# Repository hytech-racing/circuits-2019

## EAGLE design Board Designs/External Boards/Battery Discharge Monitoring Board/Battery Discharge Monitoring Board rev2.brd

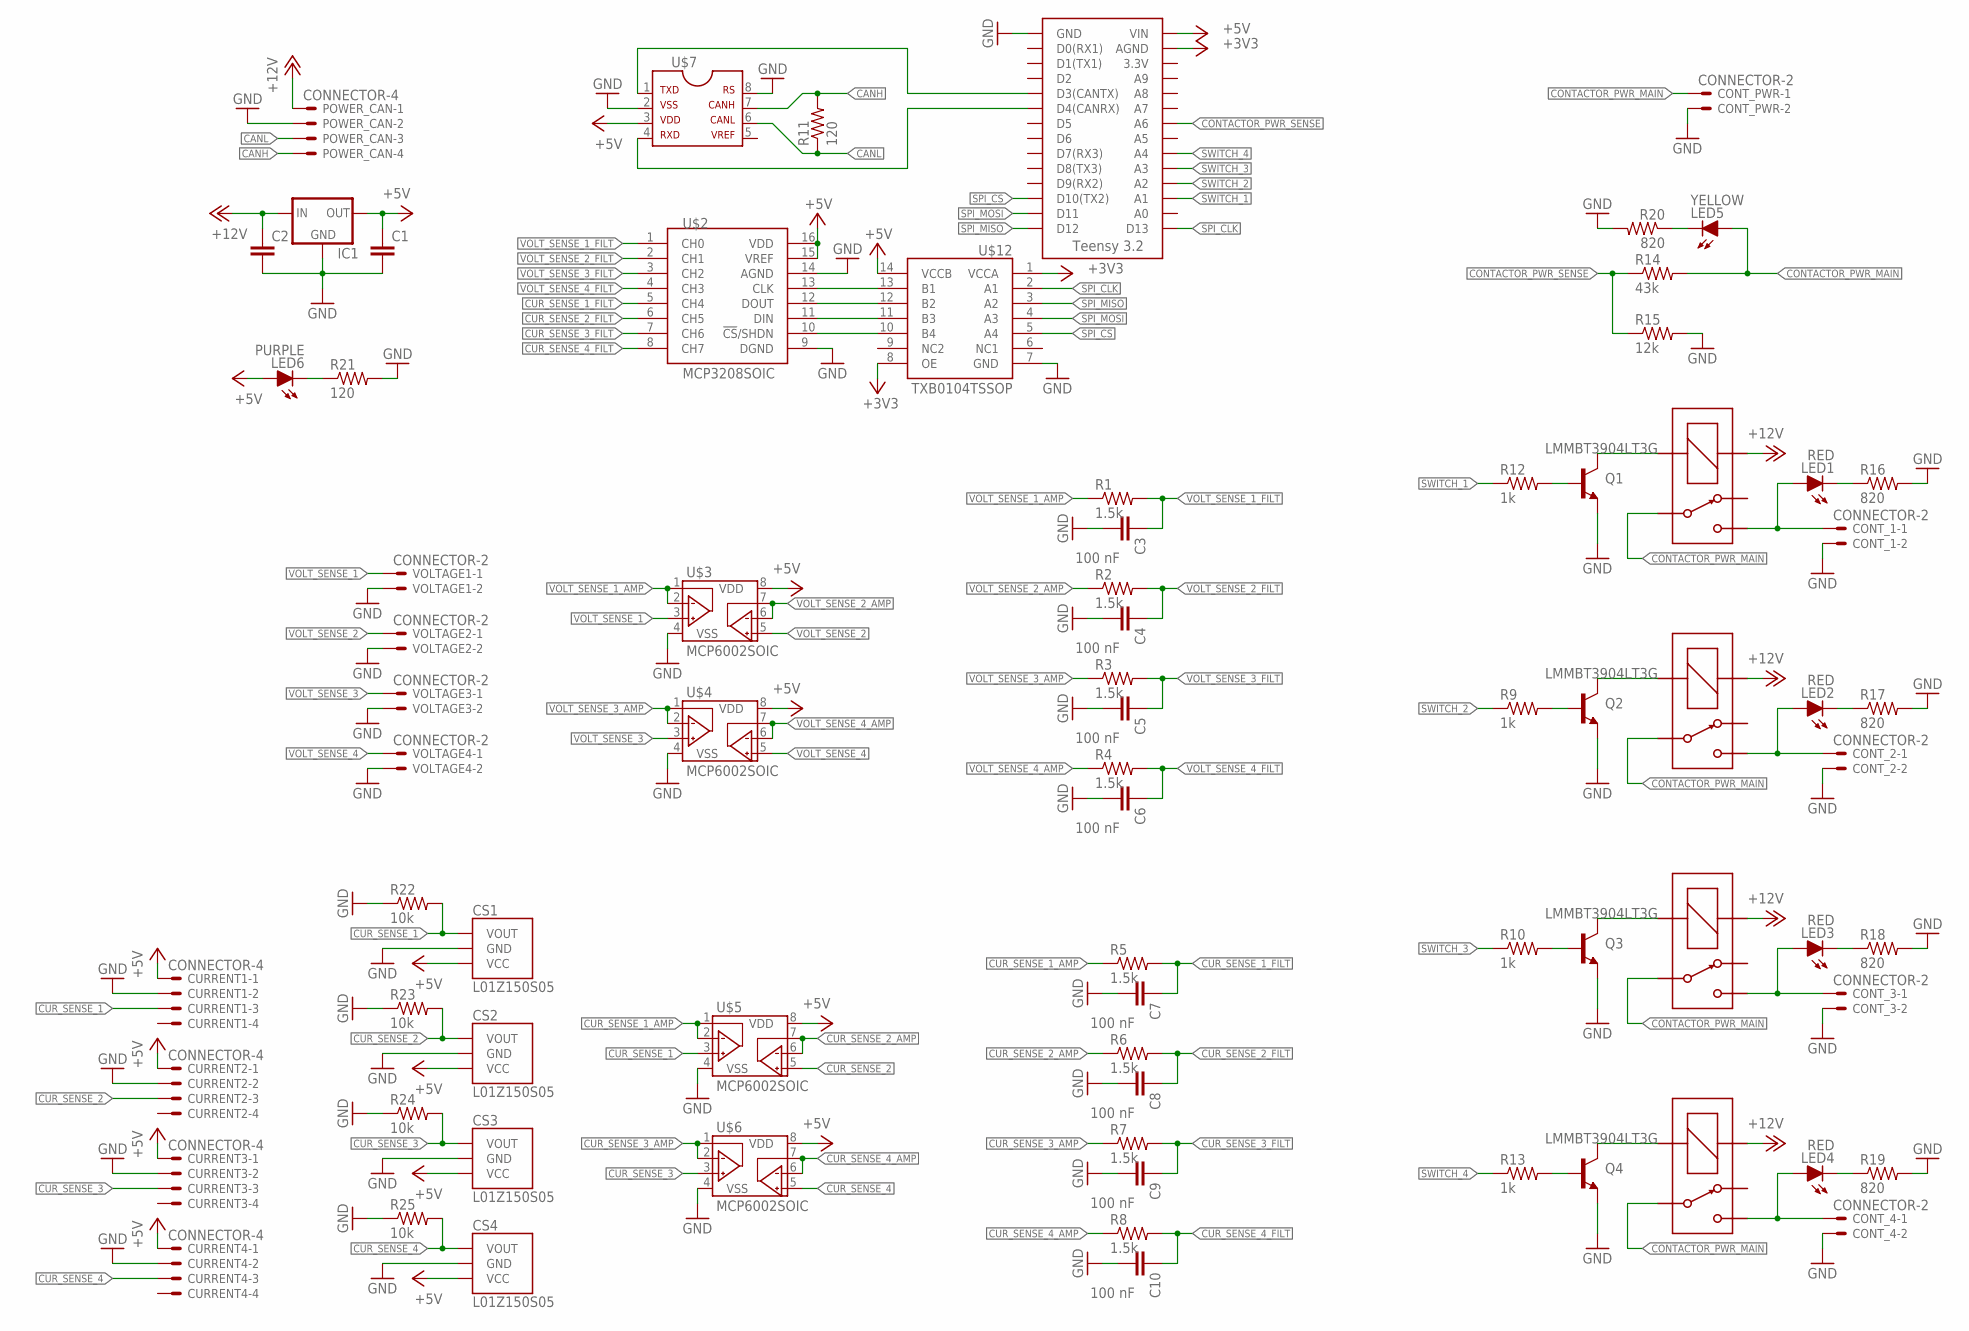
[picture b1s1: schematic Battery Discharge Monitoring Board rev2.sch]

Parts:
C1, C2: CAP0805; 0805
C3, C4, C5, C6, C7, C8, C9, C10: 100 nF; 0805
CONT_1, CONT_2, CONT_3, CONT_4: CONNECTOR-2; MINIFIT_5566-2
CONT_PWR: CONNECTOR-2; MINIFIT_5566-2
CS1, CS2, CS3, CS4: L01Z150S05
CURRENT1, CURRENT2, CURRENT3, CURRENT4: CONNECTOR-4; MINIFIT_5566-4
IC1: 5VREG_L7805SPACED; TO-220-SPACED
LED1, LED2, LED3, LED4: RED; LED-805
LED5: YELLOW; LED-805
LED6: PURPLE; LED-805
POWER_CAN: CONNECTOR-4; MINIFIT_5566-4
Q1, Q2, Q3, Q4: LMMBT3904LT3G; SOT23
R1, R2, R3, R4, R5, R6, R7, R8: 1.5k; 0805
R9, R10, R12, R13: 1k; 0805
R11, R21: 120; 0805
R14: 43k; 0805
R15: 12k; 0805
R16, R17, R18, R19, R20: 820; 0805
R22, R23, R24, R25: 10k; 0805
U$1: TEENSY_3.2_SIMPLE
U$2: MCP3208SOIC; SOIC-16
U$3, U$4, U$5, U$6: MCP6002SOIC; SOIC-08
U$7: MCP2551; SOIC-08
U$8, U$9, U$10, U$11: G5LE; ZF112
U$12: TXB0104TSSOP; TSSOP-14
VOLTAGE1, VOLTAGE2, VOLTAGE3, VOLTAGE4: CONNECTOR-2; MINIFIT_5566-2

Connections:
+3V3: U$1.AGND, U$12.1 (VCCA), U$12.8 (OE)
+5V: C1.1, CS1.3 (VCC), CS2.3 (VCC), CS3.3 (VCC), CS4.3 (VCC), CURRENT1.1, CURRENT2.1, CURRENT3.1, CURRENT4.1, IC1.3 (OUT), LED6.A, U$1.VIN, U$2.15 (VREF), U$2.16 (VDD), U$3.8 (VDD), U$4.8 (VDD), U$5.8 (VDD), U$6.8 (VDD), U$7.3, U$12.14 (VCCB)
+12V: C2.1, IC1.1 (IN), POWER_CAN.1, U$8.1 (COIL+), U$9.1 (COIL+), U$10.1 (COIL+), U$11.1 (COIL+)
CANH: POWER_CAN.4, R11.2, U$7.7
CANL: POWER_CAN.3, R11.1, U$7.6
CONTACTOR_PWR_1: CONT_1.1, LED1.A, U$8.S
CONTACTOR_PWR_2: CONT_2.1, LED2.A, U$9.S
CONTACTOR_PWR_3: CONT_3.1, LED3.A, U$10.S
CONTACTOR_PWR_4: CONT_4.1, LED4.A, U$11.S
CONTACTOR_PWR_MAIN: CONT_PWR.1, LED5.A, R14.2, U$8.P, U$9.P, U$10.P, U$11.P
CONTACTOR_PWR_SENSE: R14.1, R15.1, U$1.A6
CUR_SENSE_1: CS1.1 (VOUT), CURRENT1.3, R22.2, U$5.3 (VINA+)
CUR_SENSE_1_AMP: R5.1, U$5.1 (VOUTA), U$5.2 (VINA-)
CUR_SENSE_1_FILT: C7.1, R5.2, U$2.5 (CH4)
CUR_SENSE_2: CS2.1 (VOUT), CURRENT2.3, R23.2, U$5.5 (VINB+)
CUR_SENSE_2_AMP: R6.1, U$5.6 (VINB-), U$5.7 (VOUTB)
CUR_SENSE_2_FILT: C8.1, R6.2, U$2.6 (CH5)
CUR_SENSE_3: CS3.1 (VOUT), CURRENT3.3, R24.2, U$6.3 (VINA+)
CUR_SENSE_3_AMP: R7.1, U$6.1 (VOUTA), U$6.2 (VINA-)
CUR_SENSE_3_FILT: C9.1, R7.2, U$2.7 (CH6)
CUR_SENSE_4: CS4.1 (VOUT), CURRENT4.3, R25.2, U$6.5 (VINB+)
CUR_SENSE_4_AMP: R8.1, U$6.6 (VINB-), U$6.7 (VOUTB)
CUR_SENSE_4_FILT: C10.1, R8.2, U$2.8 (CH7)
GND: C1.2, C2.2, C3.2, C4.2, C5.2, C6.2, C7.2, C8.2, C9.2, C10.2, CONT_1.2, CONT_2.2, CONT_3.2, CONT_4.2, CONT_PWR.2, CS1.2 (GND), CS2.2 (GND), CS3.2 (GND), CS4.2 (GND), CURRENT1.2, CURRENT2.2, CURRENT3.2, CURRENT4.2, IC1.2 (GND), POWER_CAN.2, Q1.2 (EMITTER), Q2.2 (EMITTER), Q3.2 (EMITTER), Q4.2 (EMITTER), R15.2, R16.2, R17.2, R18.2, R19.2, R20.2, R21.2, R22.1, R23.1, R24.1, R25.1, U$1.GND, U$2.9 (DGND), U$2.14 (AGND), U$3.4 (VSS), U$4.4 (VSS), U$5.4 (VSS), U$6.4 (VSS), U$7.2, U$7.8, U$12.7 (GND), VOLTAGE1.2, VOLTAGE2.2, VOLTAGE3.2, VOLTAGE4.2
unnamed: U$1.D3(CANTX), U$7.1
unnamed: U$1.D4(CANRX), U$7.4
unnamed: Q2.1 (BASE), R9.2
unnamed: Q1.1 (BASE), R12.2
unnamed: Q1.3 (COLLECTOR), U$8.2 (COIL-)
unnamed: Q2.3 (COLLECTOR), U$9.2 (COIL-)
unnamed: Q3.1 (BASE), R10.2
unnamed: Q3.3 (COLLECTOR), U$10.2 (COIL-)
unnamed: Q4.1 (BASE), R13.2
unnamed: Q4.3 (COLLECTOR), U$11.2 (COIL-)
unnamed: LED2.C, R17.1
unnamed: LED1.C, R16.1
unnamed: LED3.C, R18.1
unnamed: LED4.C, R19.1
unnamed: LED5.C, R20.1
unnamed: LED6.C, R21.1
SPI_CLK: U$1.D13, U$2.13 (CLK), U$12.2 (A1), U$12.13 (B1)
SPI_CS: U$1.D10(TX2), U$2.10 (!CS!/SHDN), U$12.5 (A4), U$12.10 (B4)
SPI_MISO: U$1.D12, U$2.12 (DOUT), U$12.3 (A2), U$12.12 (B2)
SPI_MOSI: U$1.D11, U$2.11 (DIN), U$12.4 (A3), U$12.11 (B3)
SWITCH_1: R12.1, U$1.A1
SWITCH_2: R9.1, U$1.A2
SWITCH_3: R10.1, U$1.A3
SWITCH_4: R13.1, U$1.A4
VOLT_SENSE_1: U$3.3 (VINA+), VOLTAGE1.1
VOLT_SENSE_1_AMP: R1.1, U$3.1 (VOUTA), U$3.2 (VINA-)
VOLT_SENSE_1_FILT: C3.1, R1.2, U$2.1 (CH0)
VOLT_SENSE_2: U$3.5 (VINB+), VOLTAGE2.1
VOLT_SENSE_2_AMP: R2.1, U$3.6 (VINB-), U$3.7 (VOUTB)
VOLT_SENSE_2_FILT: C4.1, R2.2, U$2.2 (CH1)
VOLT_SENSE_3: U$4.3 (VINA+), VOLTAGE3.1
VOLT_SENSE_3_AMP: R3.1, U$4.1 (VOUTA), U$4.2 (VINA-)
VOLT_SENSE_3_FILT: C5.1, R3.2, U$2.3 (CH2)
VOLT_SENSE_4: U$4.5 (VINB+), VOLTAGE4.1
VOLT_SENSE_4_AMP: R4.1, U$4.6 (VINB-), U$4.7 (VOUTB)
VOLT_SENSE_4_FILT: C6.1, R4.2, U$2.4 (CH3)

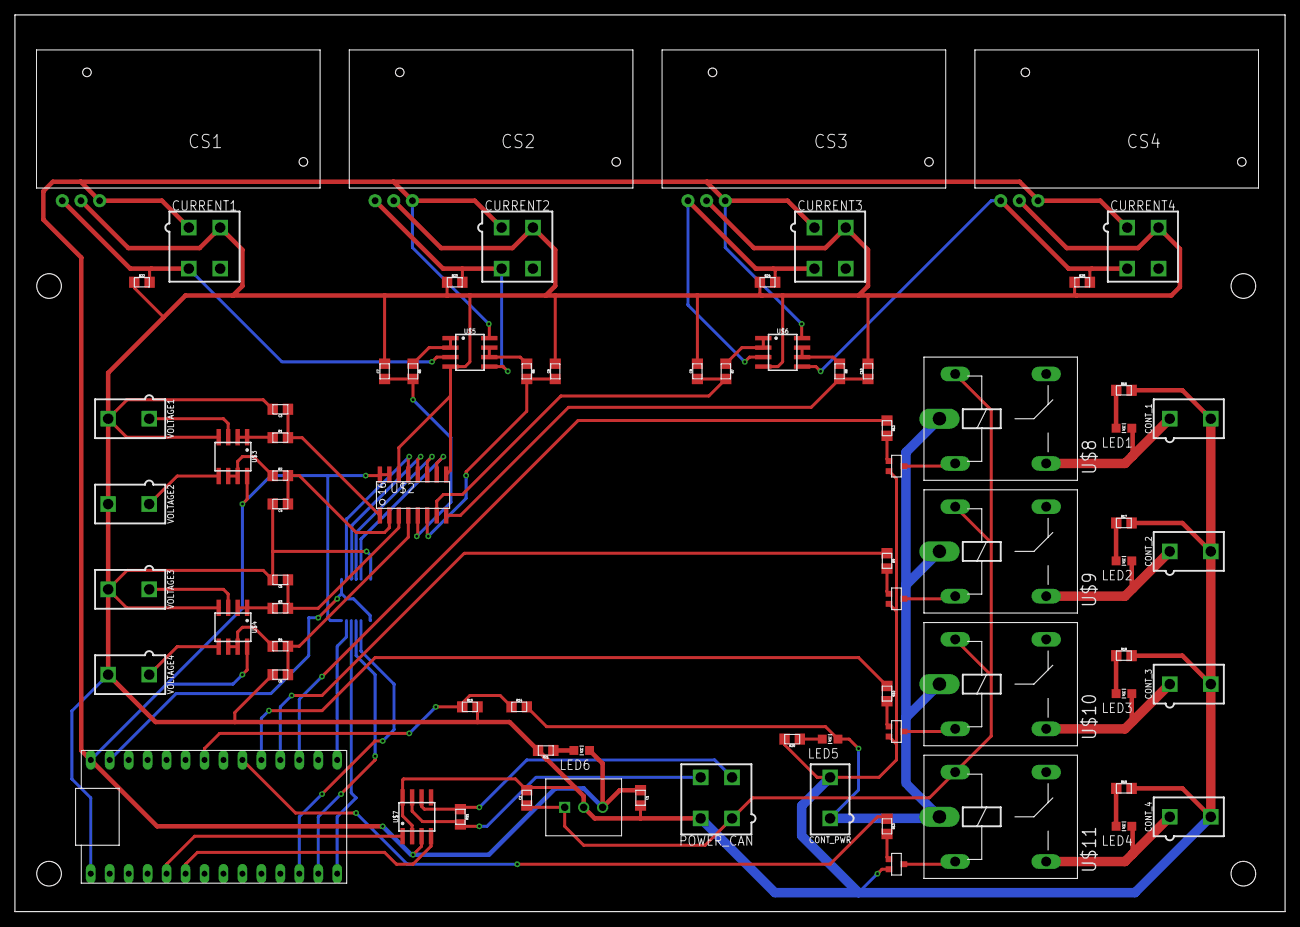
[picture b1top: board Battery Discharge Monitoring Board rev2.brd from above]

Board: 2 copper layers, 170.2 x 120.1 mm, 76 parts (1 on the bottom side), 60 nets.

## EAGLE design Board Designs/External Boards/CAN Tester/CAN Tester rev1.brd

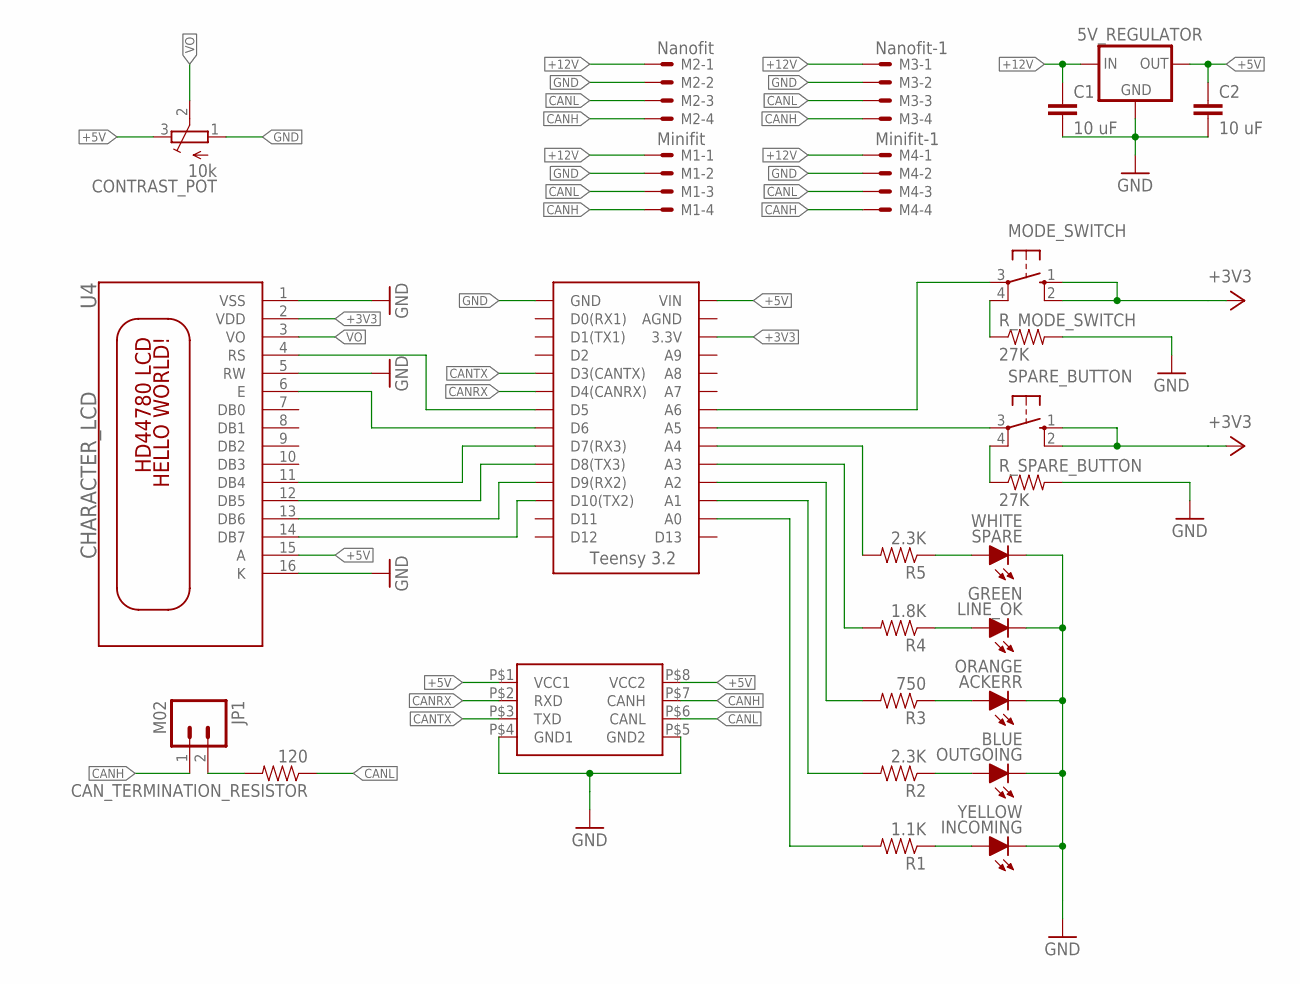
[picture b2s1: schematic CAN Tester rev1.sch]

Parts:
5V_REGULATOR: 5VREG_LM340-NLM340MPX-5.0/NOPB; SOT223
ACKERR: ORANGE; LED-805
C1, C2: 10 uF; 0805
CAN_TERMINATION_RESISTOR: 120; 0805
CONTRAST_POT: 10k; TRIM-3386
INCOMING: YELLOW; LED-805
JP1: M02; 1X02
LINE_OK: GREEN; LED-805
M1: Minifit; MINIFIT_5566-4
M2: Nanofit; NANO-FIT_VERTICAL-4
M3: Nanofit-1; NANO-FIT_VERTICAL-4
M4: Minifit-1; MINIFIT_5566-4
MODE_SWITCH: BTN_10-XX; B3F-10XX
OUTGOING: BLUE; LED-805
R1: 1.1K; 0805
R2, R5: 2.3K; 0805
R3: 750; 0805
R4: 1.8K; 0805
R_MODE_SWITCH: 27K; 0805
R_SPARE_BUTTON: 27K; 0805
SPARE: WHITE; LED-805
SPARE_BUTTON: BTN_10-XX; B3F-10XX
U1: ISOLATED CAN TRANSCIEVER; DUB8
U3: TEENSY_3.2_SIMPLE
U4: CHARACTER_LCD; LCD1602

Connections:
+3V3: MODE_SWITCH.1 (S), MODE_SWITCH.2 (S1), SPARE_BUTTON.1 (S), SPARE_BUTTON.2 (S1), U3.3.3V, U4.2 (VDD)
+5V: 5V_REGULATOR.3 (OUT), C2.1, CONTRAST_POT.3 (E), U1.P$1 (VCC1), U1.P$8 (VCC2), U3.VIN, U4.15 (A)
+12V: 5V_REGULATOR.1 (IN), C1.1, M1.1, M2.P$1, M3.P$1, M4.1
CANH: JP1.1, M1.4, M2.P$4, M3.P$4, M4.4, U1.P$7 (CANH)
CANL: CAN_TERMINATION_RESISTOR.1, CAN_TERMINATION_RESISTOR.2, JP1.2, M1.3, M2.P$3, M3.P$3, M4.3, U1.P$6 (CANL)
CANRX: U1.P$2 (RXD), U3.D4(CANRX)
CANTX: U1.P$3 (TXD), U3.D3(CANTX)
GND: 5V_REGULATOR.2 (GND), 5V_REGULATOR.4 (GND), ACKERR.C, C1.2, C2.2, CONTRAST_POT.1 (A), INCOMING.C, LINE_OK.C, M1.2, M2.P$2, M3.P$2, M4.2, OUTGOING.C, R_MODE_SWITCH.2, R_SPARE_BUTTON.2, SPARE.C, U3.GND, U4.1 (VSS), U4.5 (RW), U4.16 (K)
unnamed: R1.2, U3.A0
unnamed: R5.1, SPARE.A
unnamed: SPARE_BUTTON.3, U3.A5
unnamed: R2.2, U3.A1
unnamed: R3.2, U3.A2
unnamed: R4.2, U3.A3
unnamed: R5.2, U3.A4
unnamed: LINE_OK.A, R4.1
unnamed: ACKERR.A, R3.1
unnamed: OUTGOING.A, R2.1
unnamed: INCOMING.A, R1.1
unnamed: MODE_SWITCH.4 (P1), R_MODE_SWITCH.1
unnamed: MODE_SWITCH.3, U3.A6
unnamed: R_SPARE_BUTTON.1, SPARE_BUTTON.4 (P1)
unnamed: U1.P$4 (GND1), U1.P$5 (GND2)
unnamed: U3.D5, U4.4 (RS)
unnamed: U3.D6, U4.6 (E)
unnamed: U3.D7(RX3), U4.11 (DB4)
unnamed: U3.D8(TX3), U4.12 (DB5)
unnamed: U3.D9(RX2), U4.13 (DB6)
unnamed: U3.D10(TX2), U4.14 (DB7)
VO: CONTRAST_POT.2 (S), U4.3 (VO)

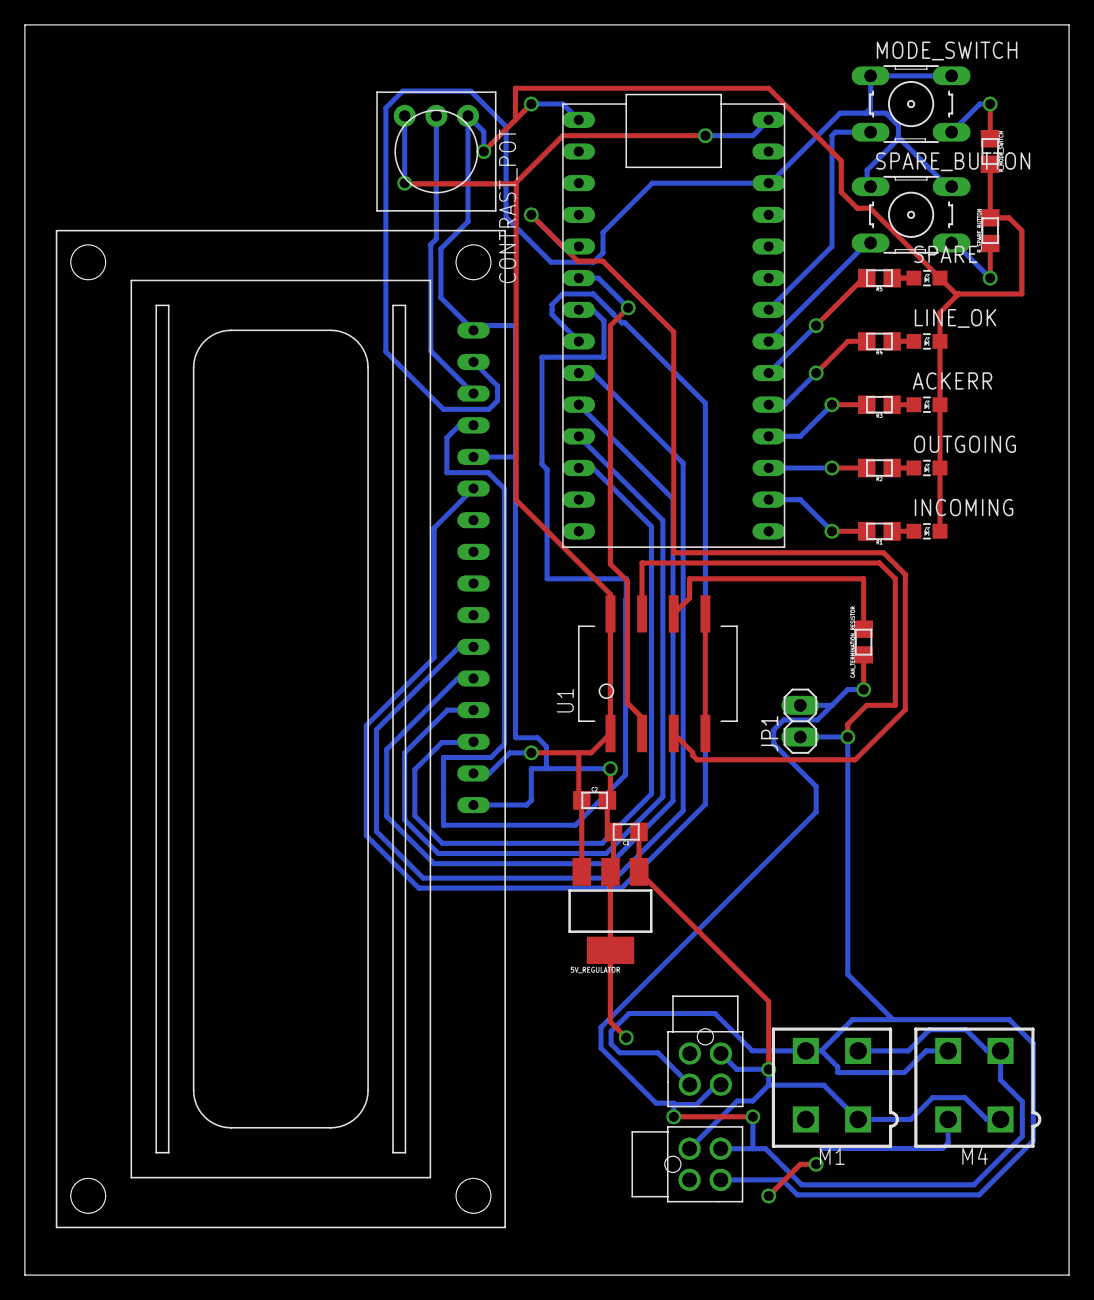
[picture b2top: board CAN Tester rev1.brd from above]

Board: 2 copper layers, 83.8 x 100.3 mm, 27 parts (0 on the bottom side), 30 nets.

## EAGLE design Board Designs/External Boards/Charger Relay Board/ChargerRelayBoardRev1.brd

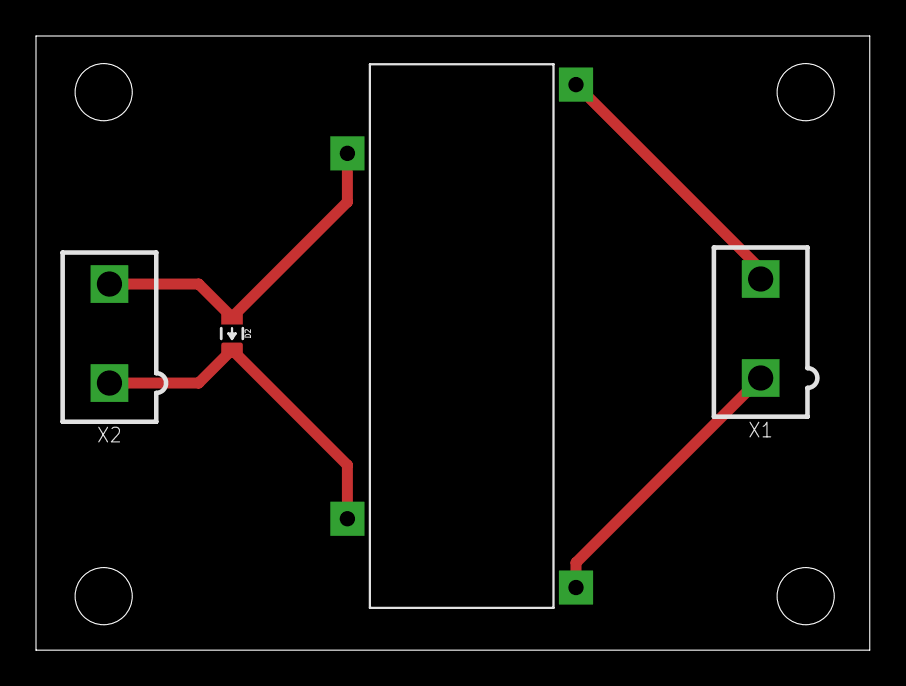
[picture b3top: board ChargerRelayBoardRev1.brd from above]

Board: 2 copper layers, 46.3 x 34.1 mm, 4 parts (0 on the bottom side), 4 nets.

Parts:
D2: DIODE0805; 0805_D
U$1: KT12-1A-40L-THT
X1, X2: CONNECTOR-2; MINIFIT_5566-2

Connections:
12V: D2.C, U$1.C1, X2.1
GND: D2.A, U$1.C2, X2.2
unnamed: U$1.S2, X1.2
unnamed: U$1.S1, X1.1

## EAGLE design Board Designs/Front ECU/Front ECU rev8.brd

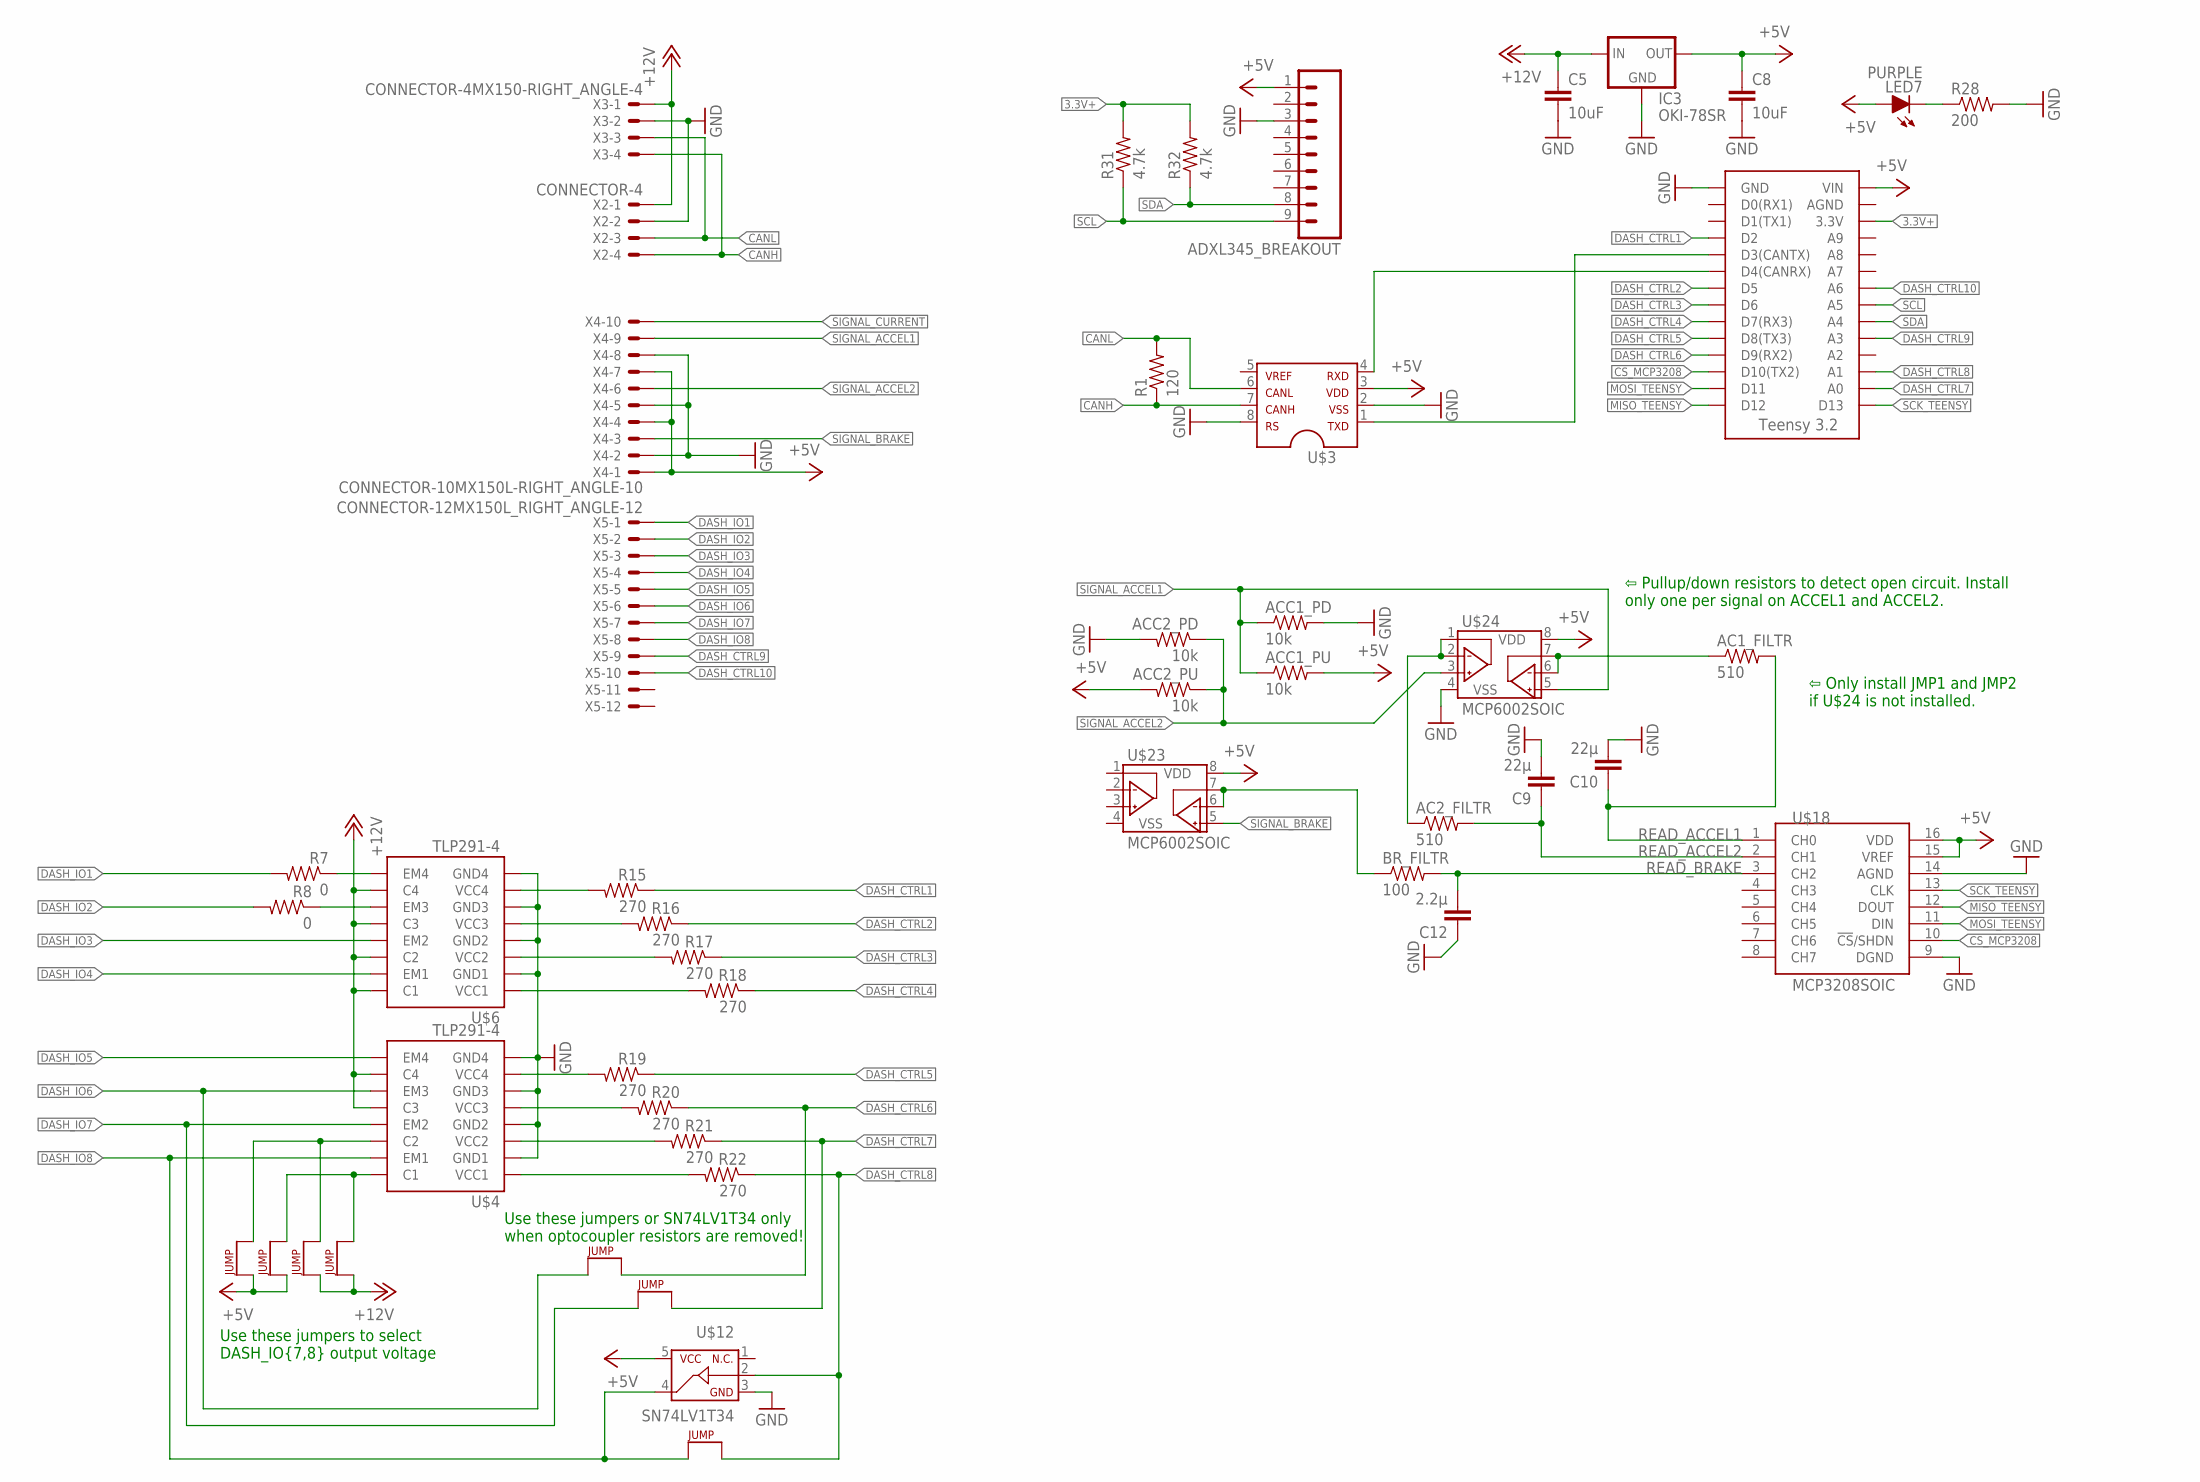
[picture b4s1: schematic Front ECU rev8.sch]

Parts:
AC1_FILTR, AC2_FILTR: 510; 0805
ACC1_PD, ACC1_PU, ACC2_PD, ACC2_PU: 10k; 0805
ADXL345_BREAKOUT: M09; 1X09
BR_FILTR: 100; 0805
C5, C8: 10uF; 0805
C9, C10: 22µ; 0805
C12: 2.2µ; 0805
IC3: OKI-78SR
LED7: PURPLE; LED-805
R1: 120; 0805
R7, R8: 0; 0805
R15, R16, R17, R18, R19, R20, R21, R22: 270; 0805
R28: 200; 0805
R31, R32: 4.7k; 0805
U$1: TEENSY_3.2_SIMPLE
U$3: MCP2551; SOIC-08
U$4, U$6: TLP291-4; SOIC-16
U$7, U$8, U$9, U$19, U$20, U$21, U$22: JUMPER; 0805
U$12: SN74LV1T34; SOT-23-5
U$18: MCP3208SOIC; SOIC-16
U$23, U$24: MCP6002SOIC; SOIC-08
X2: CONNECTOR-4; MINIFIT_5566-4
X3: CONNECTOR-4MX150-RIGHT_ANGLE-4; MX150L_RIGHT_ANGLE-4
X4: CONNECTOR-10MX150L-RIGHT_ANGLE-10; MX150L_RIGHT_ANGLE-10
X5: CONNECTOR-12MX150L_RIGHT_ANGLE-12; MX150L_RIGHT_ANGLE-12

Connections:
3.3V+: R31.2, R32.2, U$1.3.3V
+5V: ACC1_PU.2, ACC2_PU.2, ADXL345_BREAKOUT.1, C8.1, IC3.3 (OUT), LED7.A, U$1.VIN, U$3.3, U$12.5, U$18.15 (VREF), U$18.16 (VDD), U$20.1, U$22.1, U$23.8 (VDD), U$24.8 (VDD), X4.1, X4.4, X4.7
+12V: C5.1, IC3.1 (IN), U$4.10 (C4), U$4.12 (C3), U$6.10 (C4), U$6.12 (C3), U$6.14 (C2), U$6.16 (C1), U$9.1, U$21.1, X2.1, X3.P$1
CANH: R1.1, U$3.7, X2.4, X3.P$4
CANL: R1.2, U$3.6, X2.3, X3.P$3
CS_MCP3208: U$1.D10(TX2), U$18.10 (!CS!/SHDN)
DASH_CTRL1: R15.1, U$1.D2
DASH_CTRL2: R16.1, U$1.D5
DASH_CTRL3: R17.1, U$1.D6
DASH_CTRL4: R18.1, U$1.D7(RX3)
DASH_CTRL5: R19.1, U$1.D8(TX3)
DASH_CTRL6: R20.1, U$1.D9(RX2), U$7.2
DASH_CTRL7: R21.1, U$1.A0, U$8.2
DASH_CTRL8: R22.1, U$1.A1, U$12.2, U$19.2
DASH_CTRL9: U$1.A3, X5.9
DASH_CTRL10: U$1.A6, X5.10
DASH_IO1: R7.2, X5.1
DASH_IO2: R8.2, X5.2
DASH_IO3: U$6.13 (EM2), X5.3
DASH_IO4: U$6.15 (EM1), X5.4
DASH_IO5: U$4.9 (EM4), X5.5
DASH_IO6: U$4.11 (EM3), U$7.1, X5.6
DASH_IO7: U$4.13 (EM2), U$8.1, X5.7
DASH_IO8: U$4.15 (EM1), U$12.4, U$19.1, X5.8
GND: ACC1_PD.2, ACC2_PD.2, ADXL345_BREAKOUT.3, C5.2, C8.2, C9.2, C10.2, C12.1, IC3.2 (GND), R28.2, U$1.GND, U$3.2, U$3.8, U$4.2 (GND1), U$4.4 (GND2), U$4.6 (GND3), U$4.8 (GND4), U$6.2 (GND1), U$6.4 (GND2), U$6.6 (GND3), U$6.8 (GND4), U$12.3, U$18.9 (DGND), U$18.14 (AGND), U$24.4 (VSS), X2.2, X3.P$2, X4.2, X4.5, X4.8
MISO_TEENSY: U$1.D12, U$18.12 (DOUT)
MOSI_TEENSY: U$1.D11, U$18.11 (DIN)
unnamed: R7.1, U$6.9 (EM4)
unnamed: U$1.D4(CANRX), U$3.4
unnamed: R8.1, U$6.11 (EM3)
unnamed: U$4.16 (C1), U$9.2, U$20.2
unnamed: U$1.D3(CANTX), U$3.1
unnamed: U$4.14 (C2), U$21.2, U$22.2
unnamed: BR_FILTR.1, U$23.6 (VINB-), U$23.7 (VOUTB)
unnamed: AC2_FILTR.1, U$24.1 (VOUTA), U$24.2 (VINA-)
unnamed: AC1_FILTR.1, U$24.6 (VINB-), U$24.7 (VOUTB)
unnamed: R15.2, U$6.7 (VCC4)
unnamed: R16.2, U$6.5 (VCC3)
unnamed: R21.2, U$4.3 (VCC2)
unnamed: R17.2, U$6.3 (VCC2)
unnamed: R18.2, U$6.1 (VCC1)
unnamed: R19.2, U$4.7 (VCC4)
unnamed: R20.2, U$4.5 (VCC3)
unnamed: R22.2, U$4.1 (VCC1)
unnamed: LED7.C, R28.1
READ_ACCEL1: AC1_FILTR.2, C10.1, U$18.1 (CH0)
READ_ACCEL2: AC2_FILTR.2, C9.1, U$18.2 (CH1)
READ_BRAKE: BR_FILTR.2, C12.2, U$18.3 (CH2)
SCK_TEENSY: U$1.D13, U$18.13 (CLK)
SCL: ADXL345_BREAKOUT.9, R31.1, U$1.A5
SDA: ADXL345_BREAKOUT.8, R32.1, U$1.A4
SIGNAL_ACCEL1: ACC1_PD.1, ACC1_PU.1, U$24.5 (VINB+), X4.9
SIGNAL_ACCEL2: ACC2_PD.1, ACC2_PU.1, U$24.3 (VINA+), X4.6
SIGNAL_BRAKE: U$23.5 (VINB+), X4.3
SIGNAL_CURRENT: X4.10

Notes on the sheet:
Use these jumpers or SN74LV1T34 only when optocoupler resistors are removed!
Use these jumpers to select DASH_IO{7,8} output voltage
⇦ Pullup/down resistors to detect open circuit. Install only one per signal on ACCEL1 and ACCEL2.
⇦ Only install JMP1 and JMP2 if U$24 is not installed.

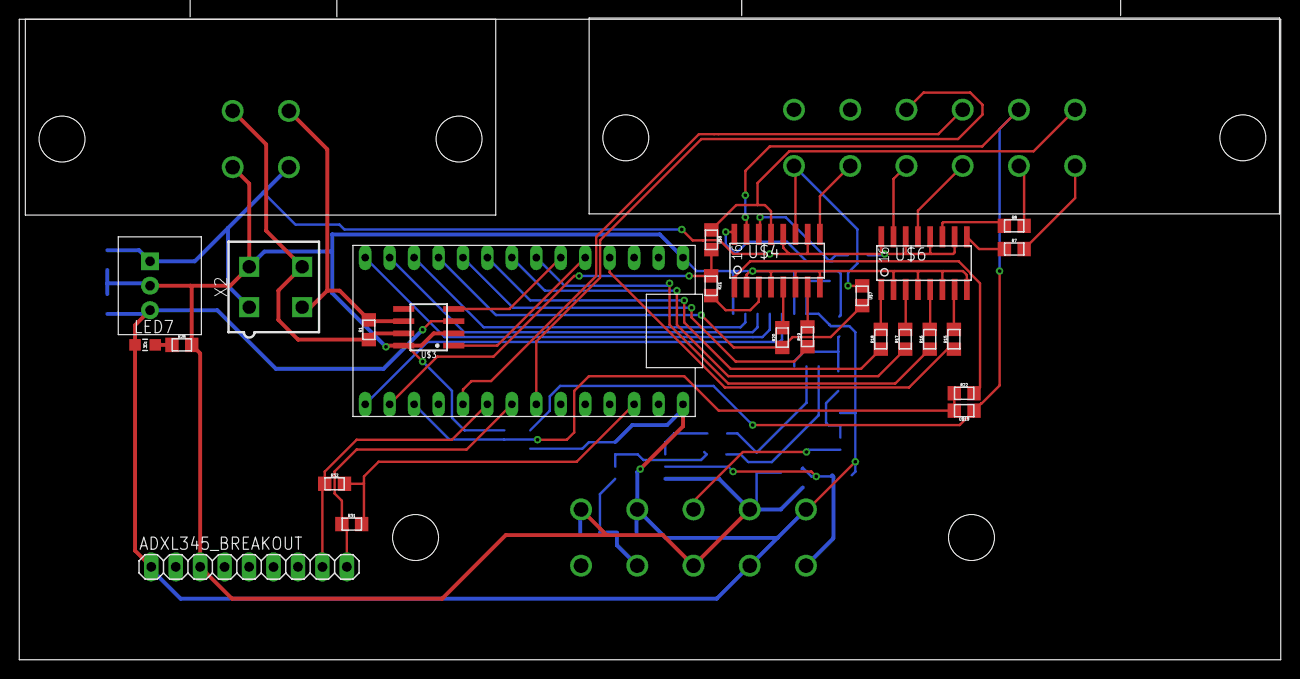
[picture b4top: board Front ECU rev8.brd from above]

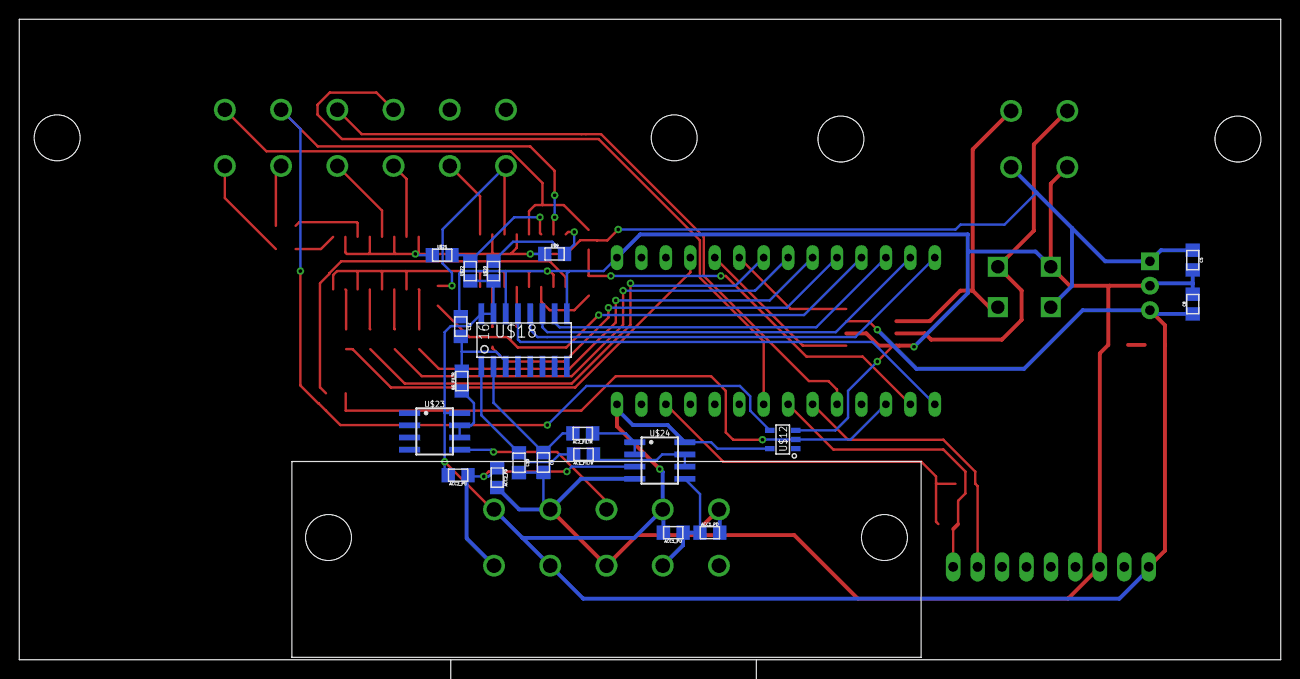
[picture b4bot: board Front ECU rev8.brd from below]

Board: 2 copper layers, 131.1 x 66.5 mm, 48 parts (21 on the bottom side), 54 nets.
